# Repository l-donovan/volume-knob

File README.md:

# volume-knob

The idea of this project is to create a simple knob with media controls.

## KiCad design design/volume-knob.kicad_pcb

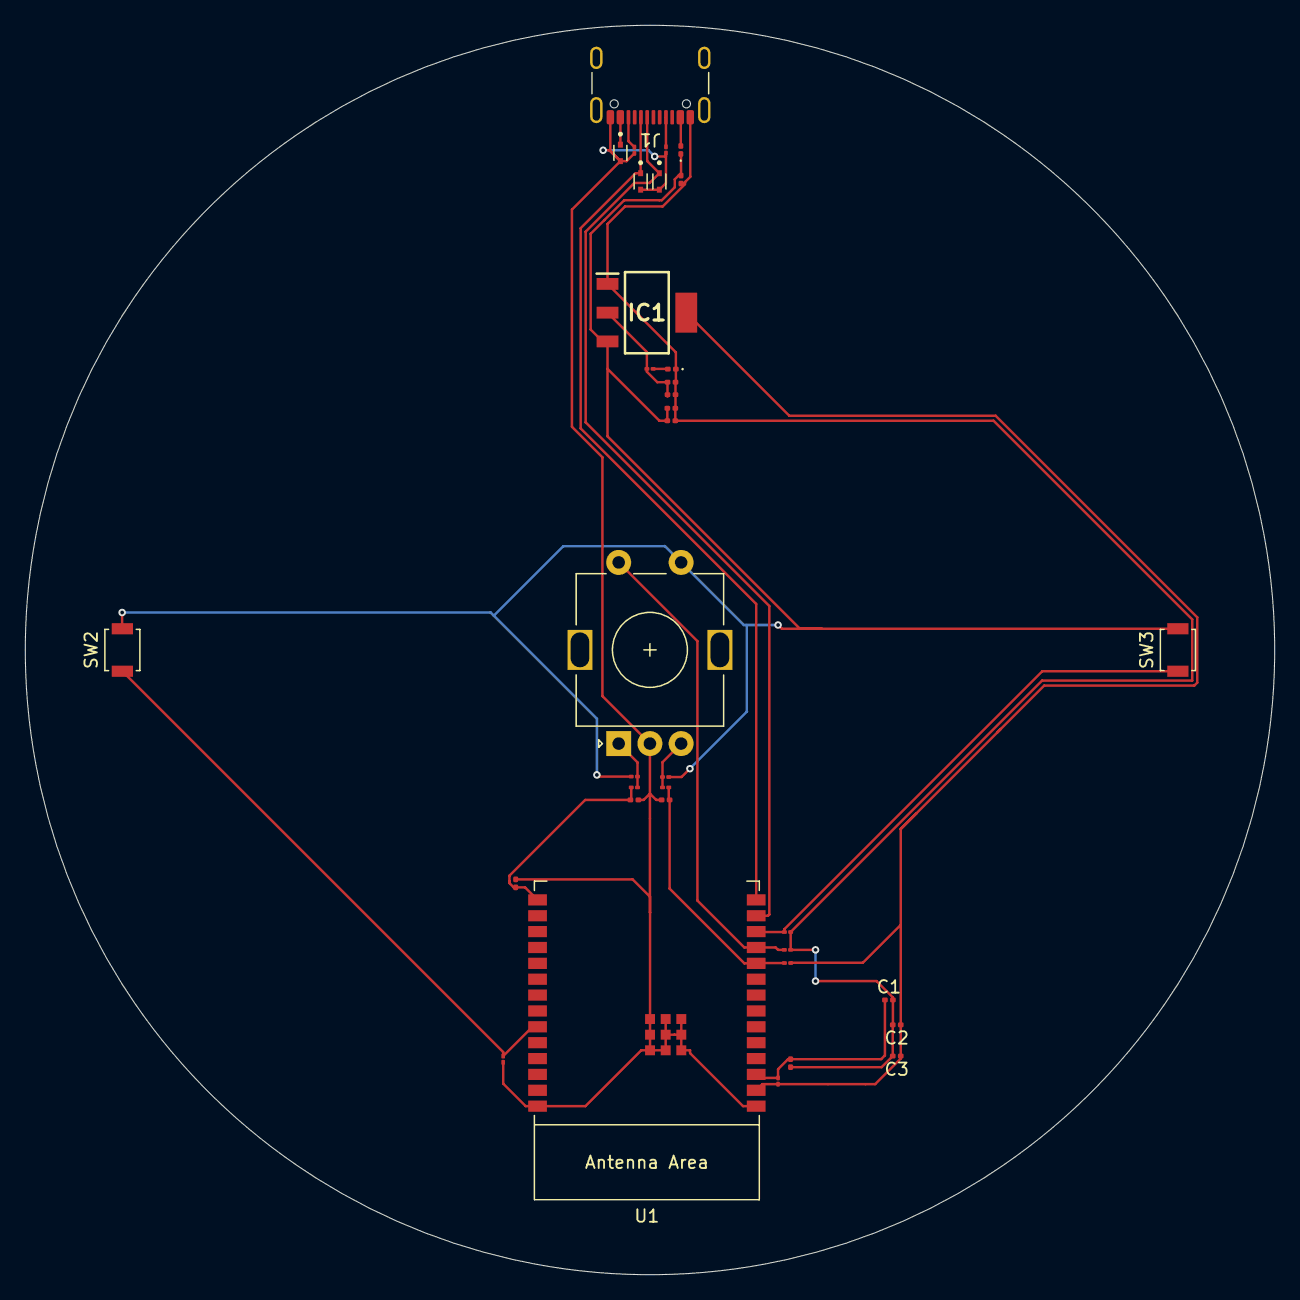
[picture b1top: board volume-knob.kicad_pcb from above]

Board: 2 copper layers, 100.0 x 100.0 mm, 35 parts (0 on the bottom side), 17 nets.

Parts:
C1: 1uF; C_0201_0603Metric
C2, C4, C5, C8: 10uF; C_0201_0603Metric
C3, C6, C7, C10, C11: 0.1uF; C_0201_0603Metric
C9, C12: C; C_0201_0603Metric
D1: D; D_0201_0603Metric
D2, D3, D4: LESD5D5.0CT1G; TVS_LESD5D5.0CT1G
D5: LED; LED_0201_0603Metric
IC1: SGM2212-3.3XKC3G_TR; SOT230P700X180-4N
J1: USB_C_Receptacle; USB_C_Receptacle_GCT_USB4105-xx-A_16P_TopMnt_Horizontal
R1, R2, R6, R11: 10K; R_01005_0402Metric
R3, R4, R5: 5.1K; R_01005_0402Metric
R7, R8, R9, R10: R_US; R_01005_0402Metric
R12: 3.3K; R_01005_0402Metric
SW1: RotaryEncoder_Switch; RotaryEncoder_Alps_EC11E-Switch_Vertical_H20mm
SW2, SW3: SW_Push; SW_SPST_B3U-1000P
U1: ESP32-C6-WROOM-1

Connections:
/EN/CHIP_PU: C1.1, C11.2, R1.2, U1.3 (EN/CHIP_PU)
/GPIO8: C9.1, R8.2, R12.2, U1.10 (GPIO8)
/GPIO9: C10.2, C12.1, R10.2, U1.15 (GPIO9)
/GPIO10: R6.1, SW1.S2, U1.11 (GPIO10)
/GPIO11: R2.2, SW3.1, U1.12 (GPIO11)
/GPIO12: D3.1, J1.A7 (D-), U1.13 (GPIO12/USB_D-)
/GPIO13: D4.1, J1.B6 (D+), U1.14 (GPIO13/USB_D+)
/GPIO15: R11.2, SW2.1, U1.23 (GPIO15)
GND: C1.2, C2.2, C3.2, C4.2, C5.2, C6.2, C7.2, C8.2, C9.2, C10.1, C11.1, C12.2, D2.2, D3.2, D4.2, D5.1 (K), IC1.1 (GND), J1.A1 (GND), J1.A12 (GND), J1.B1 (GND), J1.B12 (GND), R2.1, R3.2, R4.2, R6.2, R11.1, SW1.C, U1.1 (GND), U1.28 (GND), U1.29 (GND)
unnamed: D1.2 (A), D2.1, J1.A4 (VBUS), J1.A9 (VBUS), J1.B4 (VBUS), J1.B9 (VBUS)
unnamed: D5.2 (A), R5.2
unnamed: J1.A5 (CC1), R3.1
unnamed: J1.B5 (CC2), R4.1
unnamed: R7.2, R8.1, SW1.B
unnamed: R9.2, R10.1, SW1.A
VCC_3V3: C2.1, C3.1, C7.1, C8.1, IC1.2 (VOUT_1), IC1.4 (VOUT_2), R1.1, R5.1, R12.1, U1.2 (3V3)
VCC_5V: C4.1, C5.1, C6.1, D1.1 (K), IC1.3 (VIN), R7.1, R9.1, SW1.S1, SW2.2, SW3.2

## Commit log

2025-02-07 initialize project, add initial notes
2025-02-07 set build target
2025-02-08 add demo led project
2025-02-10 add (broken) bluetooth input implementation
2025-02-11 fix read closures
2025-02-11 refactor, simplify sending keypresses
2025-02-19 simplify button handling
2025-02-19 add initial kicad files
2025-02-19 update kicad schematic and pcb
